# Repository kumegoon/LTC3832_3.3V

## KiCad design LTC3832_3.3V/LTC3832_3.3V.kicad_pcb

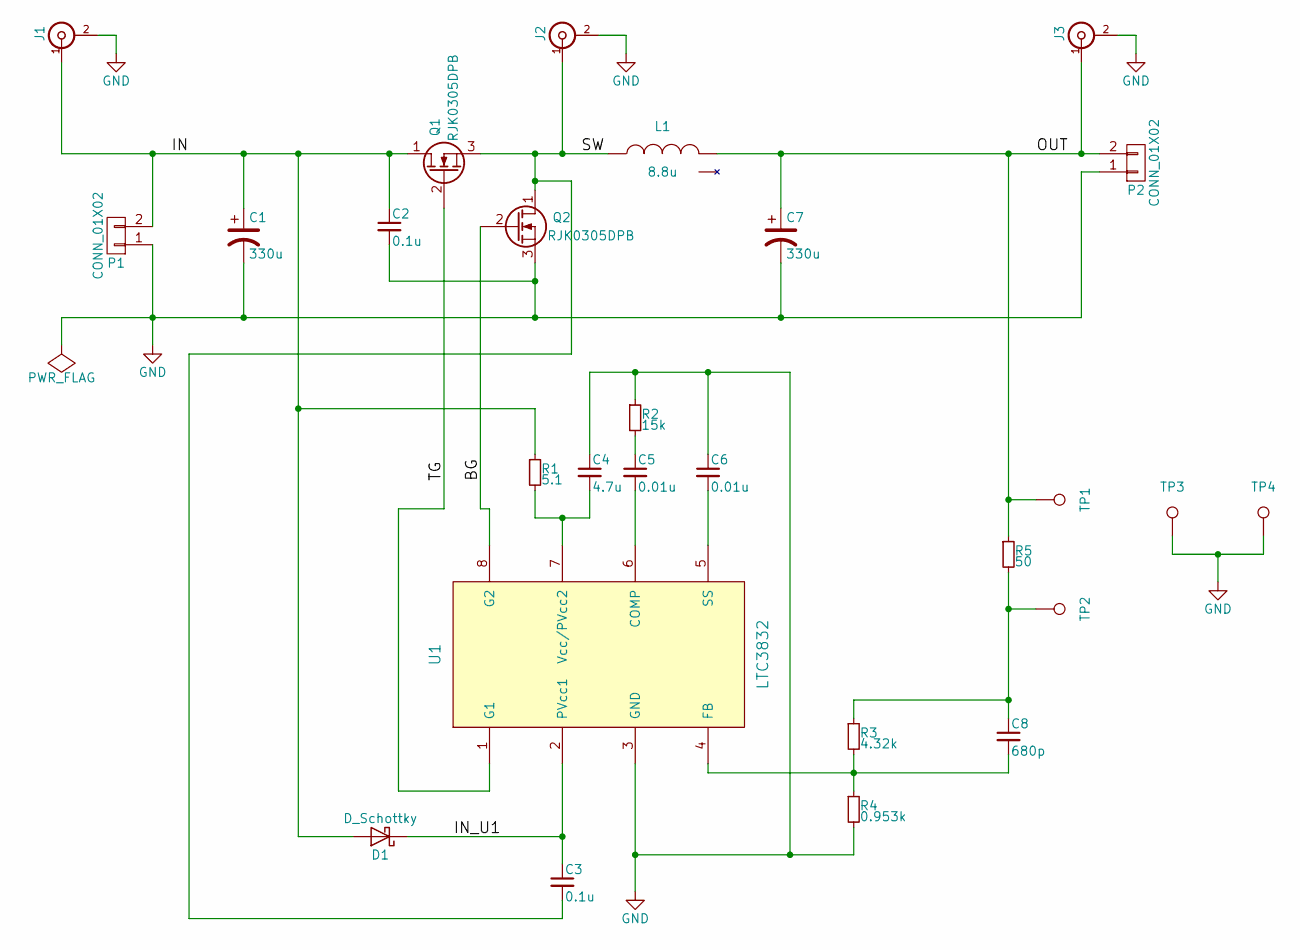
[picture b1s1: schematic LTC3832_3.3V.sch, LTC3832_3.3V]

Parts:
C1, C7: 330u; Capacitor_330uF
C2, C3: 0.1u; C1608
C4: 4.7u; C1608
C5, C6: 0.01u; C1608
C8: 680p; C1608
D1: D_Schottky; MBR0520LT
J1, J2, J3: SMA_2pin
L1: 8.8u; CDEP105
P1, P2: CONN_01X02; B2P-VH-FB-B
Q1, Q2: RJK0305DPB
R1: 5.1; R1608
R2: 15k; R1608
R3: 4.32k; R1608
R4: 0.953k; R1608
R5: 50; R1608
TP1, TP2, TP3, TP4: TEST_1P; TP_f1_0
U1: LTC3832; LTC3832-1

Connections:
/BG: Q2.2 (G), U1.8 (G2)
/IN: C1.1, C2.1, D1.2 (A), J1.1 (In), P1.2, Q1.1 (D), R1.1
/IN_U1: C3.1, D1.1 (K), U1.2 (PVcc1)
/OUT: C7.1, J3.1 (In), L1.2, P2.2, R5.1, TP1.1
/SW: C3.2, J2.1 (In), L1.1, Q1.3 (S), Q2.1 (D)
/TG: Q1.2 (G), U1.1 (G1)
GND: C1.2, C2.2, C4.1, C6.1, C7.2, J1.2 (Ext), J2.2 (Ext), J3.2 (Ext), P1.1, P2.1, Q2.3 (S), R2.1, R4.2, TP3.1, TP4.1, U1.3 (GND)
unnamed: C4.2, R1.2, U1.7 (Vcc/PVcc2)
unnamed: C5.1, R2.2
unnamed: C5.2, U1.6 (COMP)
unnamed: C6.2, U1.5 (SS)
unnamed: C8.1, R3.1, R5.2, TP2.1
unnamed: C8.2, R3.2, R4.1, U1.4 (FB)

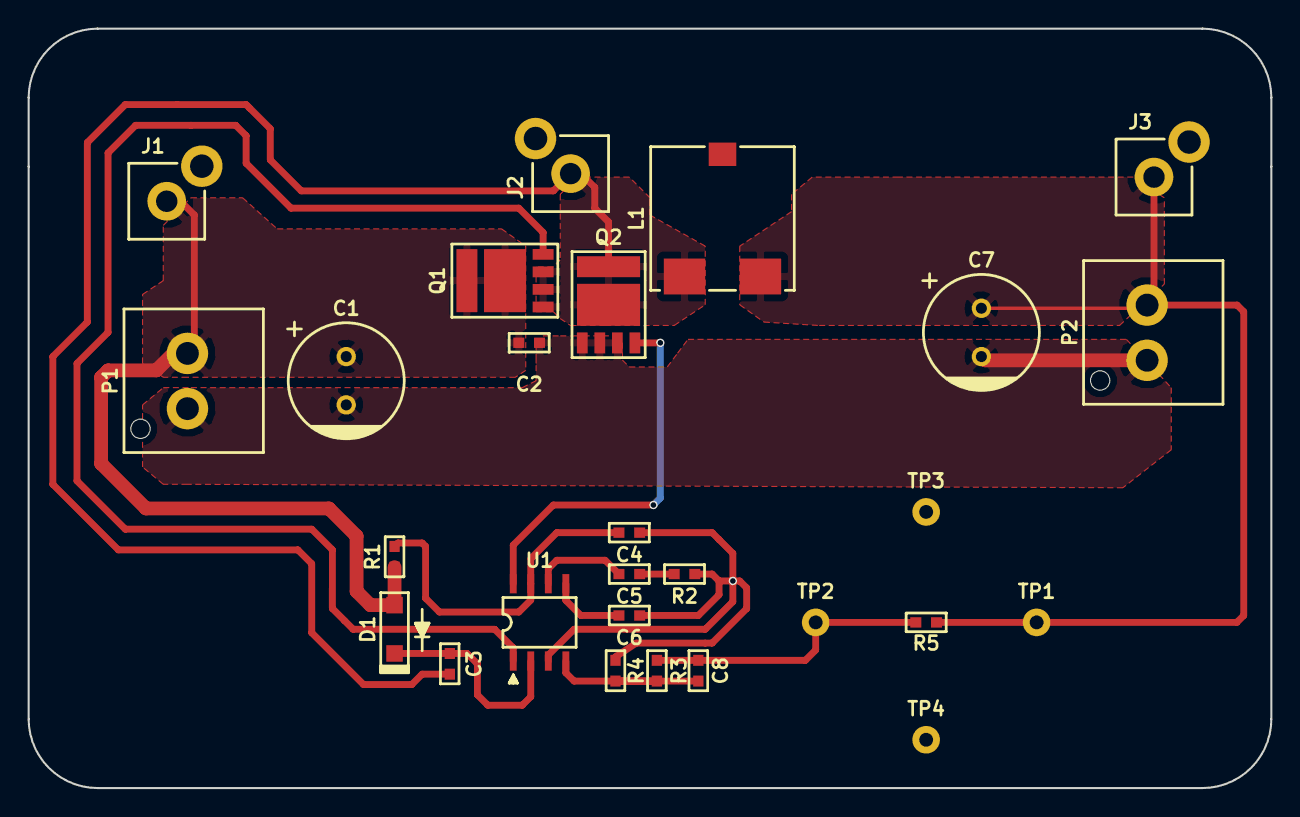
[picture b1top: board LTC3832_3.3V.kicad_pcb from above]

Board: 2 copper layers, 90.0 x 55.0 mm, 27 parts (0 on the bottom side), 13 nets.

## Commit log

2019-08-12 3.3V done
